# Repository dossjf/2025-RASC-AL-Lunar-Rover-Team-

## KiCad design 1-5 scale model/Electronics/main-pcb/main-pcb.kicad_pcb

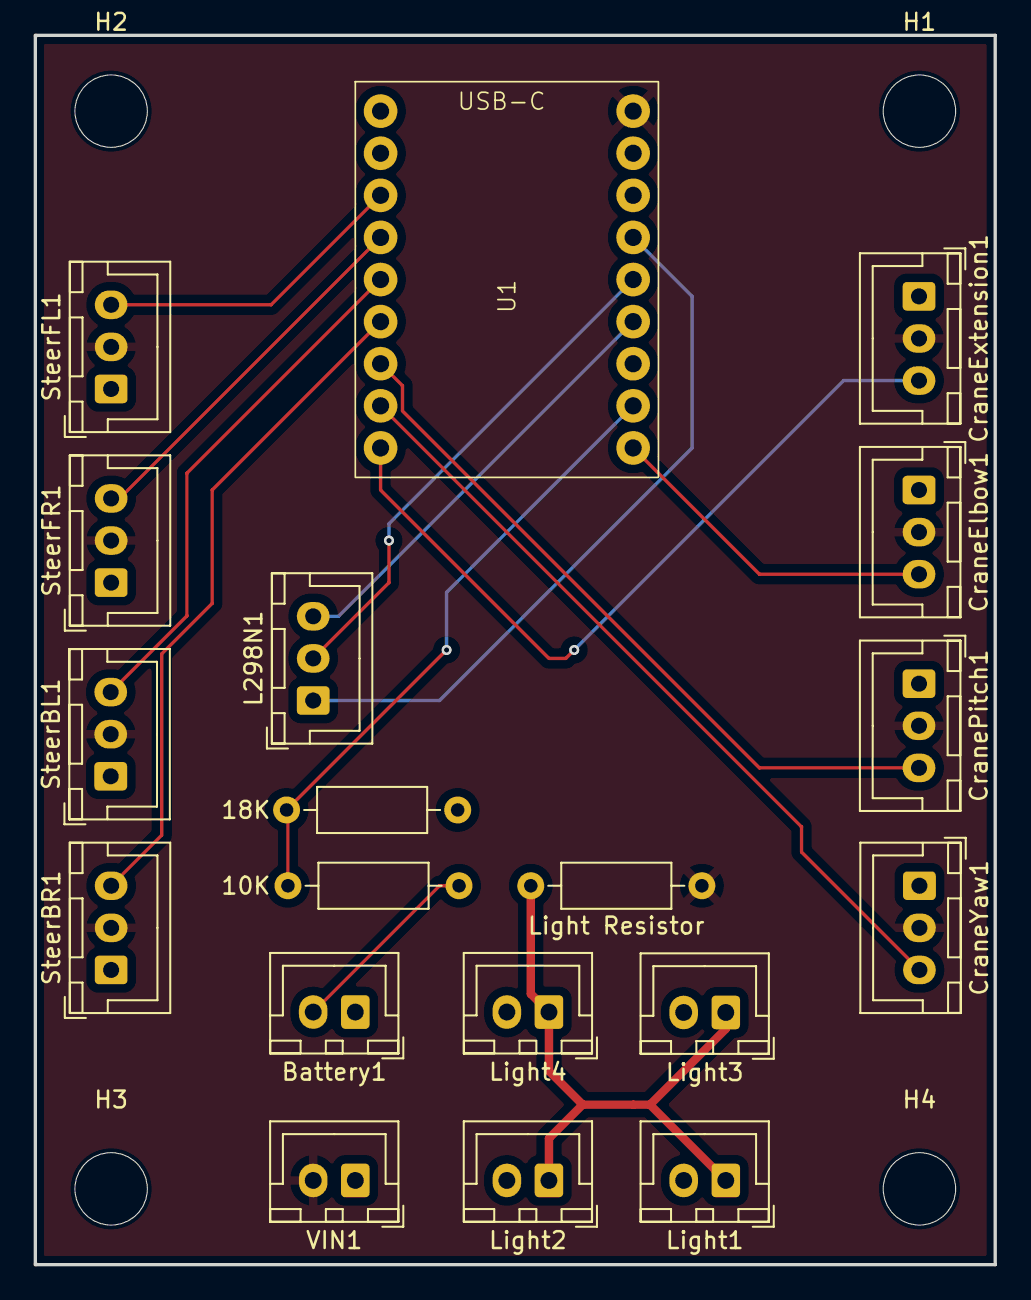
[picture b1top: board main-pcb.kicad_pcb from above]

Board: 2 copper layers, 57.0 x 73.0 mm, 23 parts (0 on the bottom side), 16 nets.

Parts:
10K: 18000; R_Axial_DIN0207_L6.3mm_D2.5mm_P10.16mm_Horizontal
18K: 10000; R_Axial_DIN0207_L6.3mm_D2.5mm_P10.16mm_Horizontal
Battery1: Battery; JST_XH_B2B-XH-A_1x02_P2.50mm_Vertical
CraneElbow1: Crame Servo Elbow; JST_XH_B3B-XH-A_1x03_P2.50mm_Vertical
CraneExtension1: Crane Servo Extension; JST_XH_B3B-XH-A_1x03_P2.50mm_Vertical
CranePitch1: Crane Servo Pitch; JST_XH_B3B-XH-A_1x03_P2.50mm_Vertical
CraneYaw1: Crane Servo Yaw; JST_XH_B3B-XH-A_1x03_P2.50mm_Vertical
H1, H2, H3, H4: MountingHole; MountingHole_4.3mm_M4
L298N1: Motor Driver (L298N); JST_XH_B3B-XH-A_1x03_P2.50mm_Vertical
Light1: Light_1; JST_XH_B2B-XH-A_1x02_P2.50mm_Vertical
Light2: Light_2; JST_XH_B2B-XH-A_1x02_P2.50mm_Vertical
Light3: Light_3; JST_XH_B2B-XH-A_1x02_P2.50mm_Vertical
Light4: Light_4; JST_XH_B2B-XH-A_1x02_P2.50mm_Vertical
Light Resistor: R; R_Axial_DIN0207_L6.3mm_D2.5mm_P10.16mm_Horizontal
SteerBL1: Steer Servo Back Left; JST_XH_B3B-XH-A_1x03_P2.50mm_Vertical
SteerBR1: Steer Servo Back Right; JST_XH_B3B-XH-A_1x03_P2.50mm_Vertical
SteerFL1: Steer Servo Front Left; JST_XH_B3B-XH-A_1x03_P2.50mm_Vertical
SteerFR1: Steer Servo Front Right; JST_XH_B3B-XH-A_1x03_P2.50mm_Vertical
U1: ESP32-S3-SUPERMINI
VIN1: VIN; JST_XH_B2B-XH-A_1x02_P2.50mm_Vertical

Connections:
+5V: CraneElbow1.2, CraneExtension1.2, CranePitch1.2, CraneYaw1.2, Light Resistor.1, SteerBL1.2, SteerBR1.2, SteerFL1.2, SteerFR1.2, U1.16 (5V), VIN1.2
Battery_Voltage_Measure: 10K.2, 18K.1, U1.9 (GP9)
Crane_Servo_Elbow: CraneElbow1.3, U1.8 (GP8)
Crane_Servo_Extension: CraneExtension1.3, U1.7 (GP7)
Crane_Servo_Pitch: CranePitch1.3, U1.5 (GP5)
Crane_Servo_Yaw: CraneYaw1.3, U1.6 (GP6)
GND: 18K.2, Battery1.1, CraneElbow1.1, CraneExtension1.1, CranePitch1.1, CraneYaw1.1, Light1.2, Light2.2, Light3.2, Light4.2, SteerBL1.1, SteerBR1.1, SteerFL1.1, SteerFR1.1, U1.15 (GND), VIN1.1
L298N_ENA: L298N1.3, U1.11 (GP11)
L298N_IN1: L298N1.1, U1.13 (GP13)
L298N_IN2: L298N1.2, U1.12 (GP12)
unnamed: 10K.1, Battery1.2
unnamed: Light1.1, Light2.1, Light3.1, Light4.1, Light Resistor.2
Signal_Steer_Servo_Back_Left: SteerBL1.3, U1.3 (GP3)
Signal_Steer_Servo_Back_Right: SteerBR1.3, U1.4 (GP4)
Signal_Steer_Servo_Front_Left: SteerFL1.3, U1.1 (GP1)
Signal_Steer_Servo_Front_Right: SteerFR1.3, U1.2 (GP2)

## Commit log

2025-03-04 rover_crane_arm
2025-03-04 start of moving wheels stuff to python
2025-03-06 Rover Gazebo
2025-03-06 yahooo
2025-03-12 remade the wheel stuff from excel to python
2025-04-01 New Rover
2025-04-02 added width calcs
2025-04-11 Updated Rover SDF File
2025-04-25 cdr wheel stuff
2025-04-29 Gazebo Test
2025-05-07 small wheel stuff
2025-05-07 intial 1-5 scale board and wire diagram
2025-05-07 updated it to be better
2025-05-07 updated pitch motor
2025-05-07 added battery voltage detector
2025-05-07 small changes
2025-05-09 gerber
2025-05-19 final changes wheels
2025-05-28 balling
2025-05-31 initial app working
2025-05-31 code that actually wokrs
